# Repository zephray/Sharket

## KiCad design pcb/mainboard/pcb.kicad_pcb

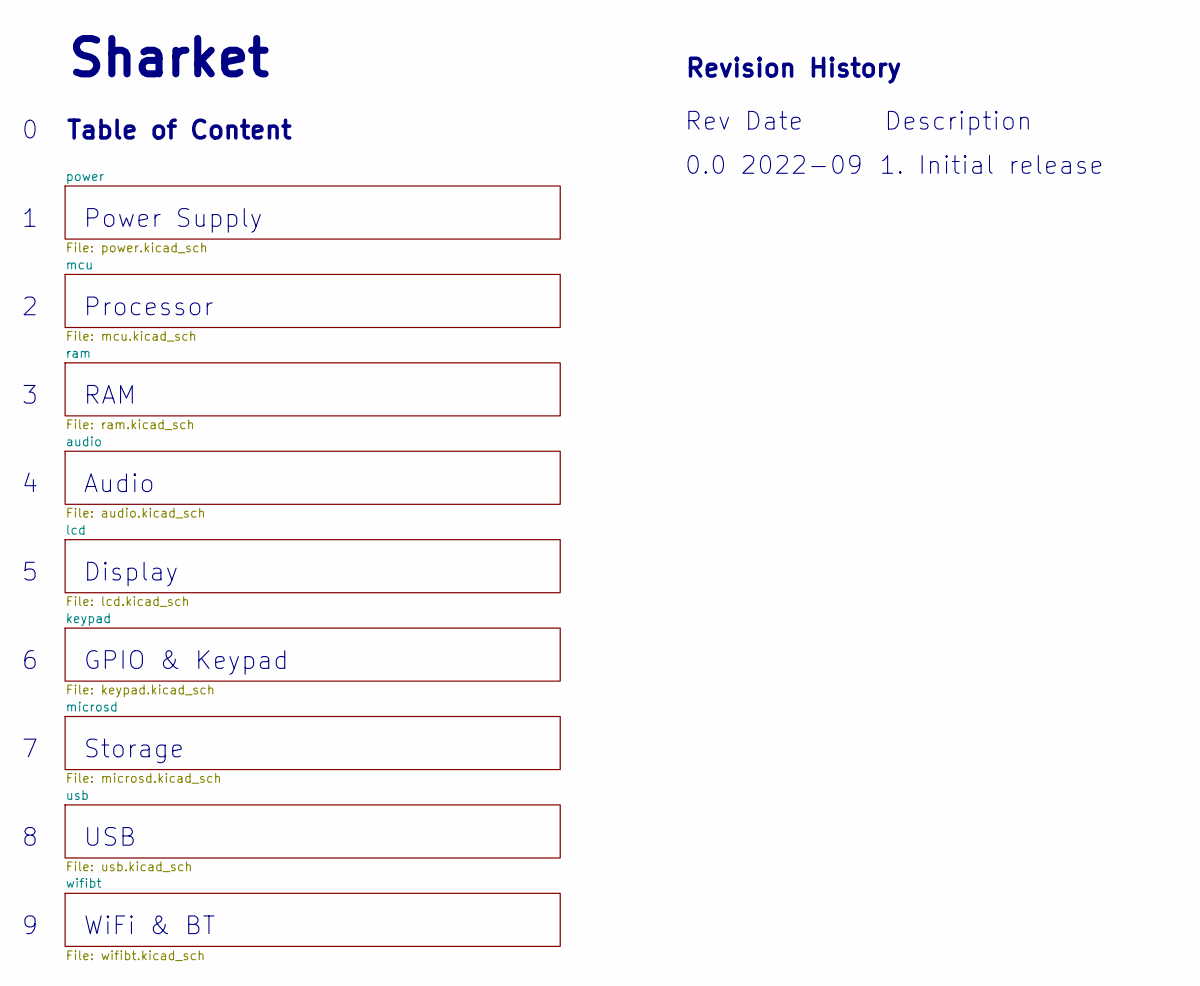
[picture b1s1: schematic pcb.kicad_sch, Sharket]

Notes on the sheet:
Storage
WiFi & BT
0.0 2022-09
Processor
Display
Revision History
Power Supply
Sharket
GPIO & Keypad
USB
Table of Content
RAM
Rev Date Description
Audio
1. Initial release

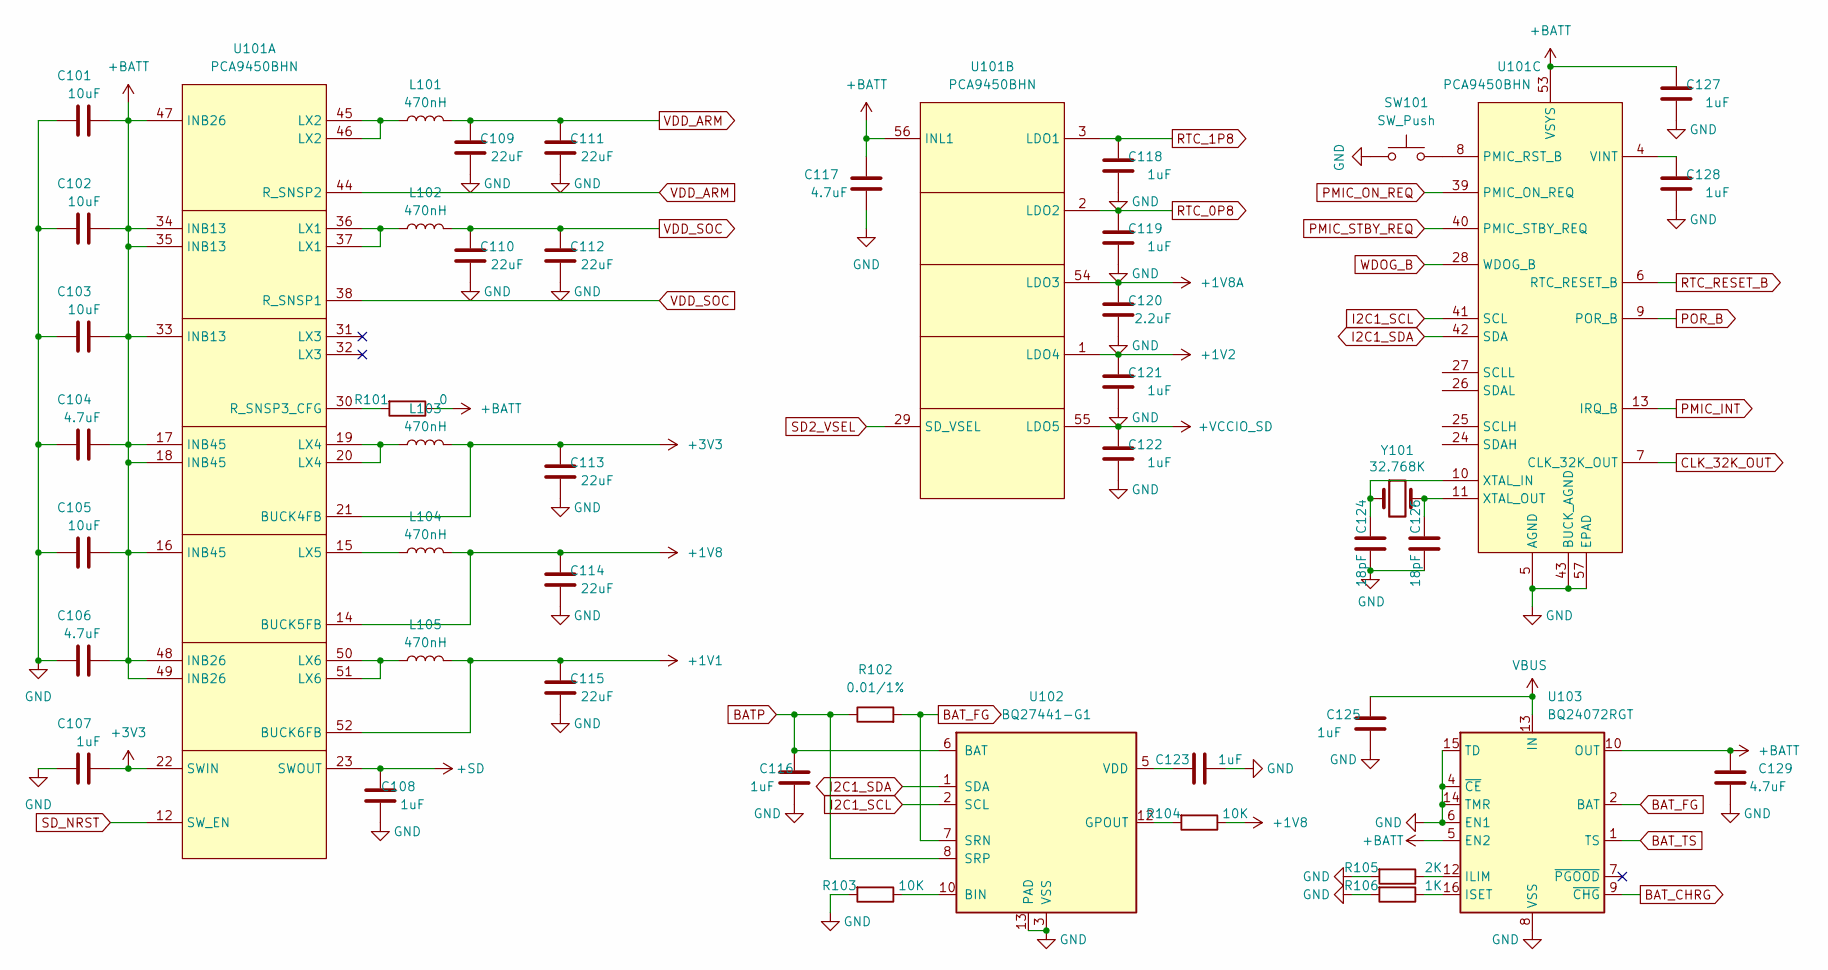
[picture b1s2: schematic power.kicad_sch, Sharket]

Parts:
C101, C102, C103, C105: 10uF; C_0603_1608Metric
C104, C106, C117, C129: 4.7uF; C_0402_1005Metric
C107, C108, C116, C123: 1uF; C_0402_1005Metric
C109, C110, C111, C112, C113, C114, C115: 22uF; C_0603_1608Metric
C118, C119, C121, C122, C125, C127, C128: 1uF; C_0201_0603Metric
C120: 2.2uF; C_0402_1005Metric
C124, C126: 18pF; C_0402_1005Metric
L101, L102, L103, L104, L105: 470nH; L_1008_2520Metric
R101: 0; R_0402_1005Metric
R102: 0.01/1%; R_0603_1608Metric
R103, R104: 10K; R_0402_1005Metric
R105: 2K; R_0402_1005Metric
R106: 1K; R_0402_1005Metric
SW101: SW_Push; SW_SPST_SKQG_WithStem
U101: PCA9450BHN; QFN-56_EP_7x7_Pitch0.4mm
U102: BQ27441-G1; Texas_S-PDSO-N12
U103: BQ24072RGT; VQFN-16-1EP_3x3mm_P0.5mm_EP1.6x1.6mm
Y101: 32.768K; Crystal_SMD_TXC_9HT11-2Pin_2.0x1.2mm_HandSoldering

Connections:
+1V1: C115.2, L105.2, U101.52 (BUCK6FB); also elsewhere on the board
+1V2: C121.2, U101.1 (LDO4); also elsewhere on the board
+1V8: C114.2, L104.2, R104.1, U101.14 (BUCK5FB); also elsewhere on the board
+1V8A: C120.2, U101.54 (LDO3); also elsewhere on the board
+3V3: C107.2, C113.2, L103.2, U101.21 (BUCK4FB), U101.22 (SWIN); also elsewhere on the board
+BATT: C101.2, C102.2, C103.2, C104.2, C105.2, C106.2, C117.2, C127.2, C129.2, R101.1, U101.16 (INB45), U101.17 (INB45), U101.18 (INB45), U101.33 (INB13), U101.34 (INB13), U101.35 (INB13), U101.47 (INB26), U101.48 (INB26), U101.49 (INB26), U101.53 (VSYS), U101.56 (INL1), U103.5 (EN2), U103.10 (OUT), U103.11 (OUT); also elsewhere on the board
+SD: C108.2, U101.23 (SWOUT); also elsewhere on the board
+VCCIO_SD: C122.2, U101.55 (LDO5); also elsewhere on the board
BATP: C116.2, R102.1, U102.6 (BAT), U102.8 (SRP); also elsewhere on the board
BAT_CHRG: U103.9 (~CHG)
BAT_FG: R102.2, U102.7 (SRN), U103.2 (BAT), U103.3 (BAT)
BAT_TS: U103.1 (TS)
CLK_32K_OUT: U101.7 (CLK_32K_OUT); also elsewhere on the board
GND: C101.1, C102.1, C103.1, C104.1, C105.1, C106.1, C107.1, C108.1, C109.1, C110.1, C111.1, C112.1, C113.1, C114.1, C115.1, C116.1, C117.1, C118.1, C119.1, C120.1, C121.1, C122.1, C123.1, C124.1, C125.1, C126.1, C127.1, C128.1, C129.1, R103.2, R105.2, R106.2, SW101.1, U101.5 (AGND), U101.43 (BUCK_AGND), U101.57 (EPAD), U102.3 (VSS), U102.13 (PAD), U103.4 (~CE), U103.6 (EN1), U103.8 (VSS), U103.14 (TMR), U103.15 (TD), U103.17 (VSS); also elsewhere on the board
I2C1_SCL: U101.41 (SCL), U102.2 (SCL); also elsewhere on the board
I2C1_SDA: U101.42 (SDA), U102.1 (SDA); also elsewhere on the board
unnamed: L101.1, U101.45 (LX2), U101.46 (LX2)
unnamed: L102.1, U101.36 (LX1), U101.37 (LX1)
unnamed: L103.1, U101.19 (LX4), U101.20 (LX4)
unnamed: L105.1, U101.50 (LX6), U101.51 (LX6)
unnamed: L104.1, U101.15 (LX5)
unnamed: R101.2, U101.30 (R_SNSP3_CFG)
unnamed: SW101.2, U101.8 (PMIC_RST_B)
unnamed: C128.2, U101.4 (VINT)
unnamed: C124.2, U101.10 (XTAL_IN), Y101.1
unnamed: C126.2, U101.11 (XTAL_OUT), Y101.2
unnamed: R103.1, U102.10 (BIN)
unnamed: R104.2, U102.12 (GPOUT)
unnamed: C123.2, U102.5 (VDD)
unnamed: R105.1, U103.12 (ILIM)
unnamed: R106.1, U103.16 (ISET)
PMIC_INT: U101.13 (IRQ_B); also elsewhere on the board
PMIC_ON_REQ: U101.39 (PMIC_ON_REQ); also elsewhere on the board
PMIC_STBY_REQ: U101.40 (PMIC_STBY_REQ); also elsewhere on the board
POR_B: U101.9 (POR_B); also elsewhere on the board
RTC_0P8: C119.2, U101.2 (LDO2); also elsewhere on the board
RTC_1P8: C118.2, U101.3 (LDO1); also elsewhere on the board
RTC_RESET_B: U101.6 (RTC_RESET_B); also elsewhere on the board
SD2_VSEL: U101.29 (SD_VSEL); also elsewhere on the board
SD_NRST: U101.12 (SW_EN); also elsewhere on the board
VBUS: C125.2, U103.13 (IN); also elsewhere on the board
VDD_ARM: C109.2, C111.2, L101.2, U101.44 (R_SNSP2); also elsewhere on the board
VDD_SOC: C110.2, C112.2, L102.2, U101.38 (R_SNSP1); also elsewhere on the board
WDOG_B: U101.28 (WDOG_B); also elsewhere on the board

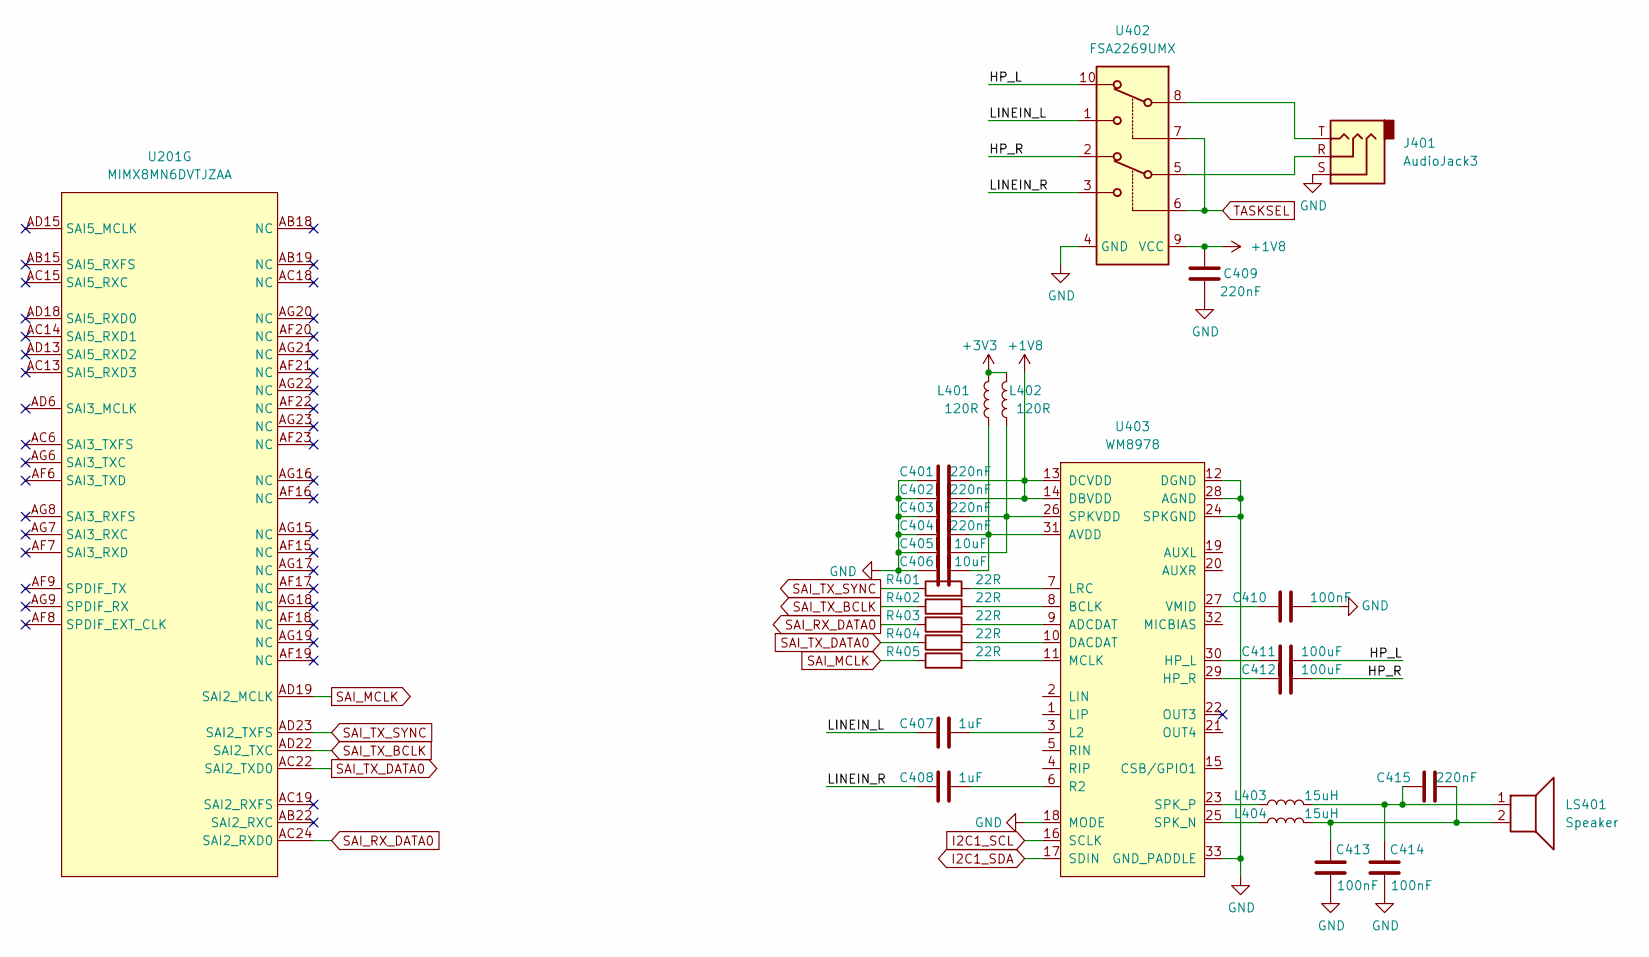
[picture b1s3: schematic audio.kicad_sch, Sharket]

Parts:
C401, C402, C403, C404, C409, C415: 220nF; C_0201_0603Metric; LCSC C880414
C405, C406: 10uF; C_0402_1005Metric; LCSC C105490
C407, C408: 1uF; C_0402_1005Metric; LCSC C157353
C410, C413, C414: 100nF; C_0201_0603Metric; LCSC C56392
C411, C412: 100uF; C_1206_3216Metric; LCSC C178304
J401: AudioJack3; PJ-208
L401, L402: 120R; L_0603_1608Metric; LCSC C76892
L403, L404: 15uH; L_0603_1608Metric; LCSC C486329
LS401: Speaker; Buzzer_CUI_CPT-9019S-SMT
R401, R402, R403, R404, R405: 22R; R_0402_1005Metric; LCSC C93929
U201: MIMX8MN6DVTJZAA; BGA-486_27x27_14.0x14.0mm
U402: FSA2269UMX; UQFN-10_1.4x1.8mm_P0.4mm
U403: WM8978; QFN-32-1EP_5x5mm_P0.5mm_EP3.45x3.45mm_ThermalVias

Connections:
+1V8: C401.1, C402.1, C409.1, U402.9 (VCC), U403.13 (DCVDD), U403.14 (DBVDD); also elsewhere on the board
+3V3: L401.2, L402.2; also elsewhere on the board
/audio/HP_L: C411.2, U402.10
/audio/HP_R: C412.2, U402.2
/audio/LINEIN_L: C407.2, U402.1
/audio/LINEIN_R: C408.2, U402.3
GND: C401.2, C402.2, C403.2, C404.2, C405.2, C406.2, C409.2, C410.2, C413.1, C414.1, J401.S, U402.4 (GND), U403.12 (DGND), U403.18 (MODE), U403.24 (SPKGND), U403.28 (AGND), U403.33 (GND_PADDLE); also elsewhere on the board
I2C1_SCL: U403.16 (SCLK); also elsewhere on the board
I2C1_SDA: U403.17 (SDIN); also elsewhere on the board
unnamed: C413.2, C415.2, L404.2, LS401.2
unnamed: C414.2, C415.1, L403.2, LS401.1
unnamed: J401.R, U402.5
unnamed: J401.T, U402.8
unnamed: R403.2, U403.9 (ADCDAT)
unnamed: C404.1, C406.1, L401.1, U403.31 (AVDD)
unnamed: R402.2, U403.8 (BCLK)
unnamed: R404.2, U403.10 (DACDAT)
unnamed: C411.1, U403.30 (HP_L)
unnamed: C412.1, U403.29 (HP_R)
unnamed: C407.1, U403.3 (L2)
unnamed: R401.2, U403.7 (LRC)
unnamed: R405.2, U403.11 (MCLK)
unnamed: C408.1, U403.6 (R2)
unnamed: C403.1, C405.1, L402.1, U403.26 (SPKVDD)
unnamed: L404.1, U403.25 (SPK_N)
unnamed: L403.1, U403.23 (SPK_P)
unnamed: C410.1, U403.27 (VMID)
SAI_MCLK: R405.1, U201.AD19 (SAI2_MCLK)
SAI_RX_DATA0: R403.1, U201.AC24 (SAI2_RXD0)
SAI_TX_BCLK: R402.1, U201.AD22 (SAI2_TXC)
SAI_TX_DATA0: R404.1, U201.AC22 (SAI2_TXD0)
SAI_TX_SYNC: R401.1, U201.AD23 (SAI2_TXFS)
TASKSEL: U402.6, U402.7; also elsewhere on the board

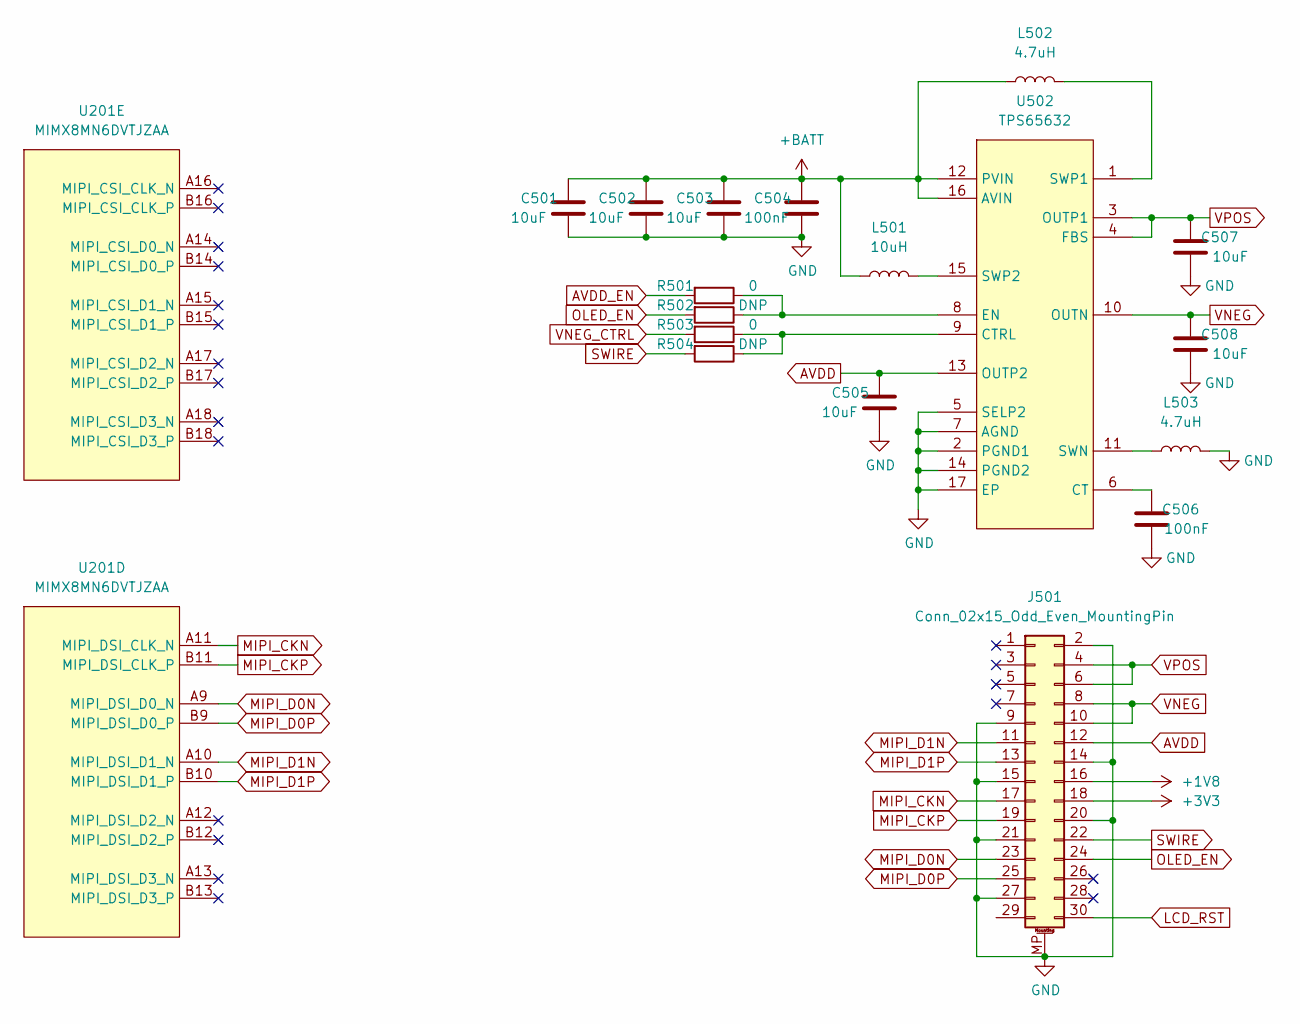
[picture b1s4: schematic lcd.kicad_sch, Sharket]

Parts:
C501, C502, C503, C505, C507, C508: 10uF; C_0603_1608Metric
C504, C506: 100nF; C_0201_0603Metric
J501: Conn_02x15_Odd_Even_MountingPin; 505270-3012
L501: 10uH; L_1008_2520Metric
L502, L503: 4.7uH; L_1008_2520Metric
R501, R503: 0; R_0402_1005Metric
R502, R504: DNP; R_0402_1005Metric
U201: MIMX8MN6DVTJZAA; BGA-486_27x27_14.0x14.0mm
U502: TPS65632; QFN-16-1EP_3x3mm_P0.5mm_EP1.7x1.7mm

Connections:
+1V8: J501.16; also elsewhere on the board
+3V3: J501.18; also elsewhere on the board
+BATT: C501.2, C502.2, C503.2, C504.2, L501.1, L502.1, U502.12 (PVIN), U502.16 (AVIN); also elsewhere on the board
AVDD: C505.2, J501.12, U502.13 (OUTP2)
AVDD_EN: R501.2; also elsewhere on the board
GND: C501.1, C502.1, C503.1, C504.1, C505.1, C506.1, C507.1, C508.1, J501.2, J501.9, J501.14, J501.15, J501.20, J501.21, J501.27, J501.MP (MountPin), L503.2, U502.2 (PGND1), U502.5 (SELP2), U502.7 (AGND), U502.14 (PGND2), U502.17 (EP); also elsewhere on the board
LCD_RST: J501.30; also elsewhere on the board
MIPI_CKN: J501.17, U201.A11 (MIPI_DSI_CLK_N)
MIPI_CKP: J501.19, U201.B11 (MIPI_DSI_CLK_P)
MIPI_D0N: J501.23, U201.A9 (MIPI_DSI_D0_N)
MIPI_D0P: J501.25, U201.B9 (MIPI_DSI_D0_P)
MIPI_D1N: J501.11, U201.A10 (MIPI_DSI_D1_N)
MIPI_D1P: J501.13, U201.B10 (MIPI_DSI_D1_P)
unnamed: C506.2, U502.6 (CT)
unnamed: R503.1, R504.1, U502.9 (CTRL)
unnamed: R501.1, R502.1, U502.8 (EN)
unnamed: L503.1, U502.11 (SWN)
unnamed: L502.2, U502.1 (SWP1)
unnamed: L501.2, U502.15 (SWP2)
OLED_EN: J501.24, R502.2
SWIRE: J501.22, R504.2
VNEG: C508.2, J501.8, J501.10, U502.10 (OUTN)
VNEG_CTRL: R503.2; also elsewhere on the board
VPOS: C507.2, J501.4, J501.6, U502.3 (OUTP1), U502.4 (FBS)

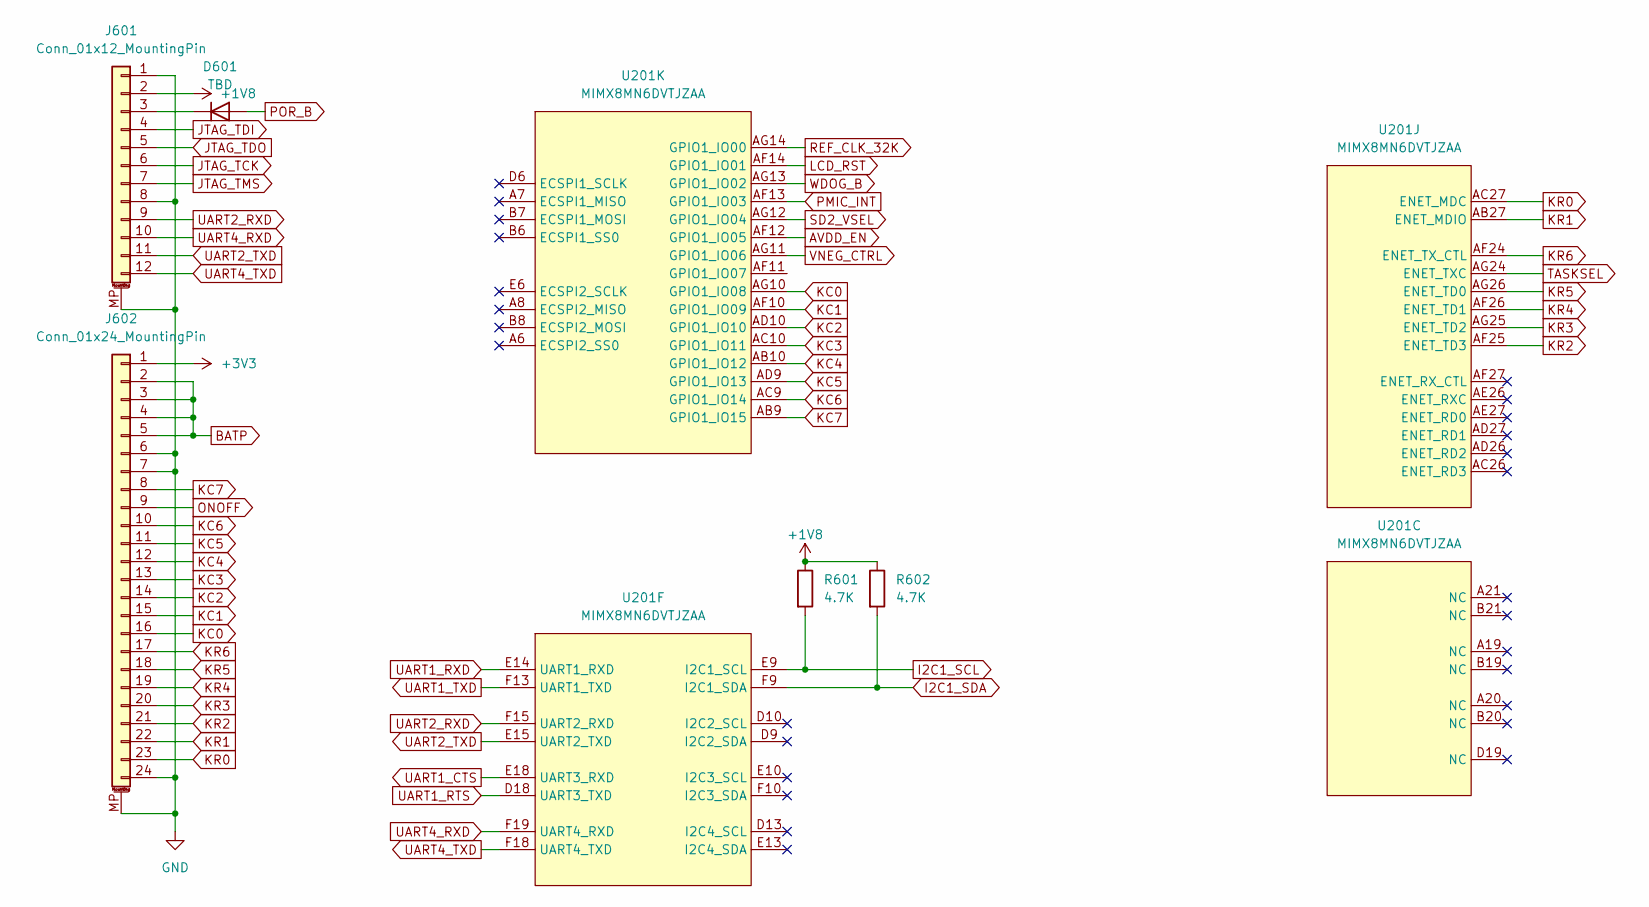
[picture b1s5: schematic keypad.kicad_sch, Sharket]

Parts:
D601: TBD; D_SOD-323
J601: Conn_01x12_MountingPin; TE_1-1734839-2_1x12-1MP_P0.5mm_Horizontal
J602: Conn_01x24_MountingPin; TE_2-1734839-4_1x24-1MP_P0.5mm_Horizontal
R601, R602: 4.7K; R_0402_1005Metric
U201: MIMX8MN6DVTJZAA; BGA-486_27x27_14.0x14.0mm

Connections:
+1V8: J601.2, R601.1, R602.1; also elsewhere on the board
+3V3: J602.1; also elsewhere on the board
AVDD_EN: U201.AF12 (GPIO1_IO05); also elsewhere on the board
BATP: J602.2, J602.3, J602.4, J602.5; also elsewhere on the board
GND: J601.1, J601.8, J601.MP (MountPin), J602.6, J602.7, J602.24, J602.MP (MountPin); also elsewhere on the board
I2C1_SCL: R601.2, U201.E9 (I2C1_SCL); also elsewhere on the board
I2C1_SDA: R602.2, U201.F9 (I2C1_SDA); also elsewhere on the board
JTAG_TCK: J601.6; also elsewhere on the board
JTAG_TDI: J601.4; also elsewhere on the board
JTAG_TDO: J601.5; also elsewhere on the board
JTAG_TMS: J601.7; also elsewhere on the board
KC0: J602.16, U201.AG10 (GPIO1_IO08)
KC1: J602.15, U201.AF10 (GPIO1_IO09)
KC2: J602.14, U201.AD10 (GPIO1_IO10)
KC3: J602.13, U201.AC10 (GPIO1_IO11)
KC4: J602.12, U201.AB10 (GPIO1_IO12)
KC5: J602.11, U201.AD9 (GPIO1_IO13)
KC6: J602.10, U201.AC9 (GPIO1_IO14)
KC7: J602.8, U201.AB9 (GPIO1_IO15)
KR0: J602.23, U201.AC27 (ENET_MDC)
KR1: J602.22, U201.AB27 (ENET_MDIO)
KR2: J602.21, U201.AF25 (ENET_TD3)
KR3: J602.20, U201.AG25 (ENET_TD2)
KR4: J602.19, U201.AF26 (ENET_TD1)
KR5: J602.18, U201.AG26 (ENET_TD0)
KR6: J602.17, U201.AF24 (ENET_TX_CTL)
LCD_RST: U201.AF14 (GPIO1_IO01); also elsewhere on the board
unnamed: D601.1 (K), J601.3
ONOFF: J602.9; also elsewhere on the board
PMIC_INT: U201.AF13 (GPIO1_IO03); also elsewhere on the board
POR_B: D601.2 (A); also elsewhere on the board
REF_CLK_32K: U201.AG14 (GPIO1_IO00); also elsewhere on the board
SD2_VSEL: U201.AG12 (GPIO1_IO04); also elsewhere on the board
TASKSEL: U201.AG24 (ENET_TXC); also elsewhere on the board
UART1_CTS: U201.E18 (UART3_RXD); also elsewhere on the board
UART1_RTS: U201.D18 (UART3_TXD); also elsewhere on the board
UART1_RXD: U201.E14 (UART1_RXD); also elsewhere on the board
UART1_TXD: U201.F13 (UART1_TXD); also elsewhere on the board
UART2_RXD: J601.9, U201.F15 (UART2_RXD)
UART2_TXD: J601.11, U201.E15 (UART2_TXD)
UART4_RXD: J601.10, U201.F19 (UART4_RXD)
UART4_TXD: J601.12, U201.F18 (UART4_TXD)
VNEG_CTRL: U201.AG11 (GPIO1_IO06); also elsewhere on the board
WDOG_B: U201.AG13 (GPIO1_IO02); also elsewhere on the board

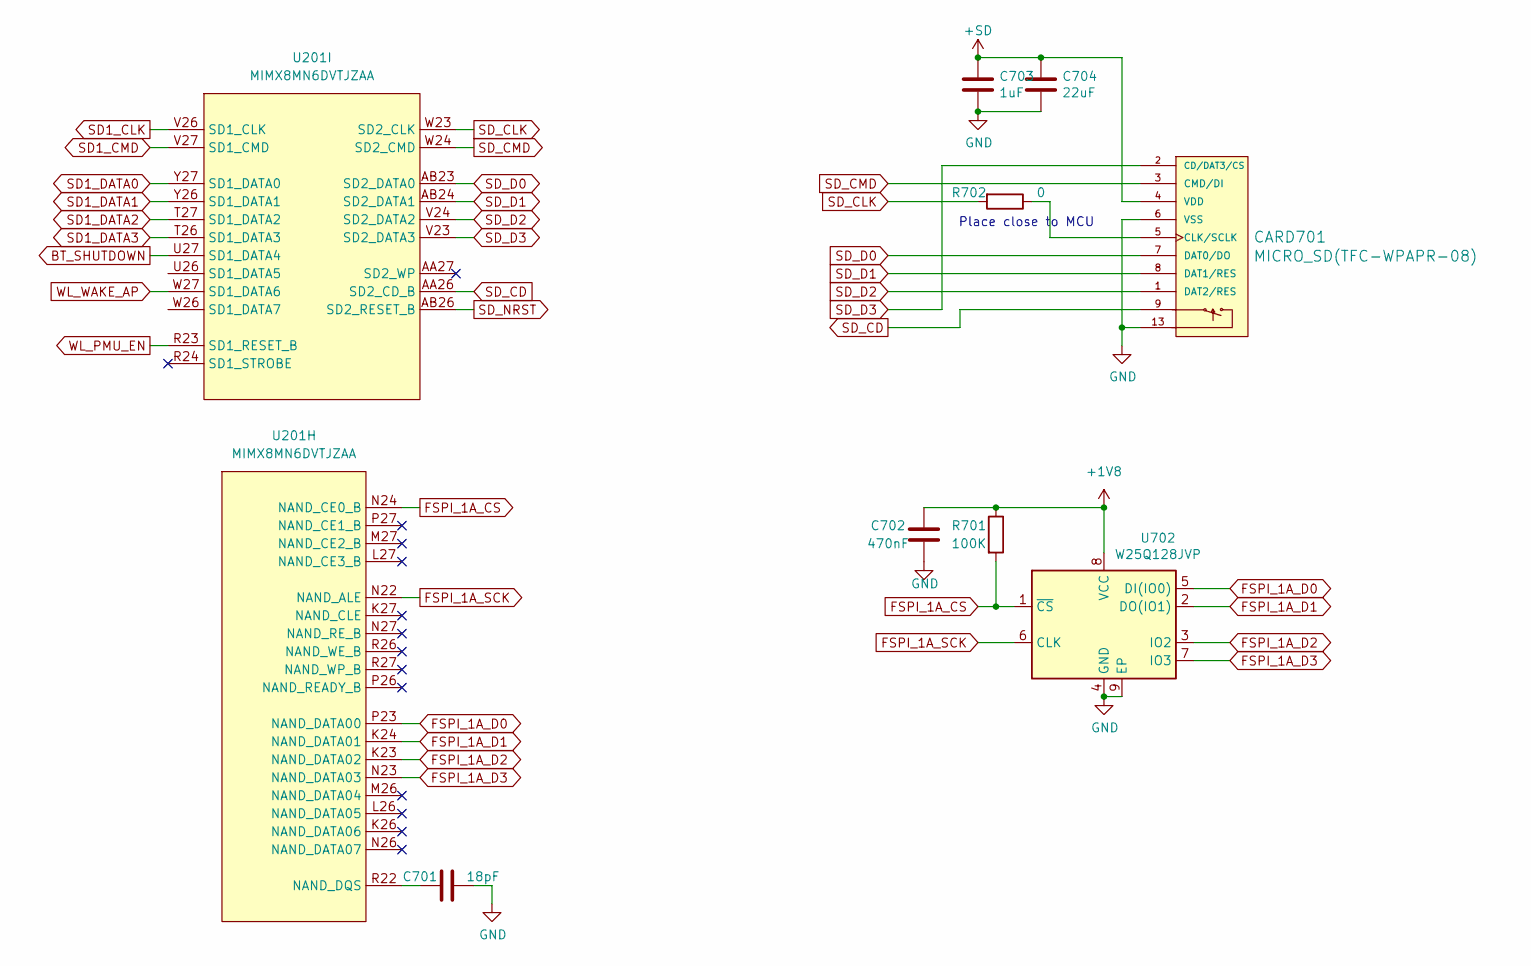
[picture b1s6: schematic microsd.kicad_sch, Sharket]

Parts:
C701: 18pF; C_0402_1005Metric
C702: 470nF; C_0402_1005Metric
C703: 1uF; C_0402_1005Metric
C704: 22uF; C_0603_1608Metric
CARD701: MICRO_SD(TFC-WPAPR-08); TFC-WPAPR-08
R701: 100K; R_0402_1005Metric
R702: 0; R_0402_1005Metric
U201: MIMX8MN6DVTJZAA; BGA-486_27x27_14.0x14.0mm
U702: W25Q128JVP; WSON-8-1EP_6x5mm_P1.27mm_EP3.4x4.3mm

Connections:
+1V8: C702.2, R701.1, U702.8 (VCC); also elsewhere on the board
+SD: C703.1, C704.1, CARD701.4 (VDD); also elsewhere on the board
BT_SHUTDOWN: U201.U27 (SD1_DATA4); also elsewhere on the board
FSPI_1A_CS: R701.2, U201.N24 (NAND_CE0_B), U702.1 (~CS)
FSPI_1A_D0: U201.P23 (NAND_DATA00), U702.5 (DI(IO0))
FSPI_1A_D1: U201.K24 (NAND_DATA01), U702.2 (DO(IO1))
FSPI_1A_D2: U201.K23 (NAND_DATA02), U702.3 (IO2)
FSPI_1A_D3: U201.N23 (NAND_DATA03), U702.7 (IO3)
FSPI_1A_SCK: U201.N22 (NAND_ALE), U702.6 (CLK)
GND: C701.1, C702.1, C703.2, C704.2, CARD701.6 (VSS), CARD701.10, CARD701.11, CARD701.12, CARD701.13, U702.4 (GND), U702.9 (EP); also elsewhere on the board
unnamed: CARD701.5 (CLK/SCLK), R702.1
unnamed: C701.2, U201.R22 (NAND_DQS)
SD1_CLK: U201.V26 (SD1_CLK); also elsewhere on the board
SD1_CMD: U201.V27 (SD1_CMD); also elsewhere on the board
SD1_DATA0: U201.Y27 (SD1_DATA0); also elsewhere on the board
SD1_DATA1: U201.Y26 (SD1_DATA1); also elsewhere on the board
SD1_DATA2: U201.T27 (SD1_DATA2); also elsewhere on the board
SD1_DATA3: U201.T26 (SD1_DATA3); also elsewhere on the board
SD_CD: CARD701.9, U201.AA26 (SD2_CD_B)
SD_CLK: R702.2, U201.W23 (SD2_CLK)
SD_CMD: CARD701.3 (CMD/DI), U201.W24 (SD2_CMD)
SD_D0: CARD701.7 (DAT0/DO), U201.AB23 (SD2_DATA0)
SD_D1: CARD701.8 (DAT1/RES), U201.AB24 (SD2_DATA1)
SD_D2: CARD701.1 (DAT2/RES), U201.V24 (SD2_DATA2)
SD_D3: CARD701.2 (CD/DAT3/CS), U201.V23 (SD2_DATA3)
SD_NRST: U201.AB26 (SD2_RESET_B); also elsewhere on the board
WL_PMU_EN: U201.R23 (SD1_RESET_B); also elsewhere on the board
WL_WAKE_AP: U201.W27 (SD1_DATA6); also elsewhere on the board

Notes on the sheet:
Place close to MCU

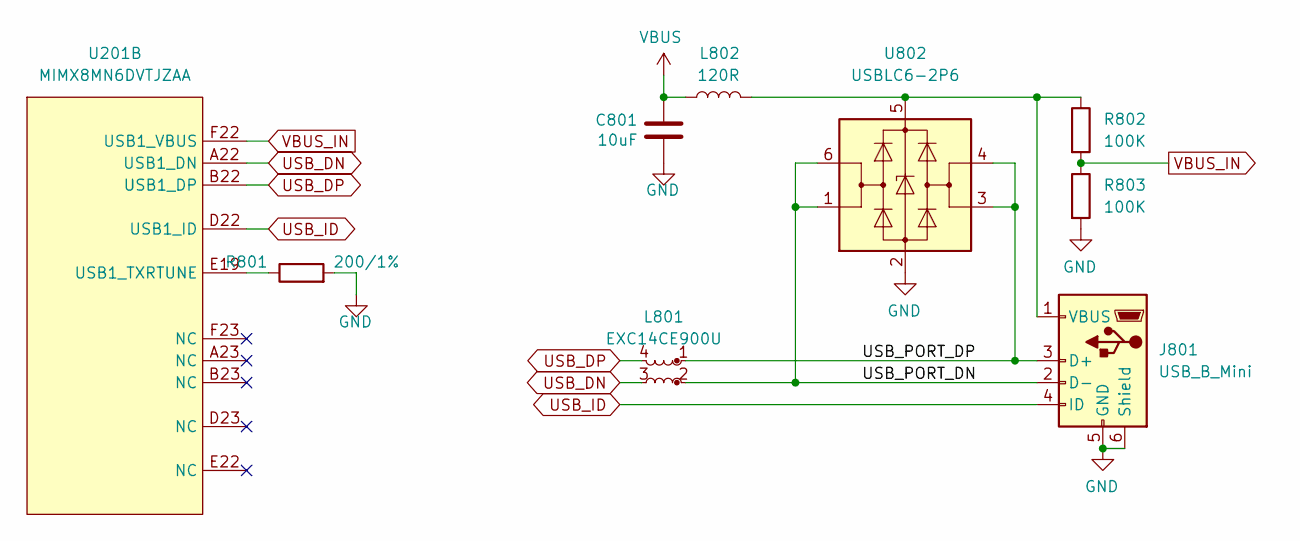
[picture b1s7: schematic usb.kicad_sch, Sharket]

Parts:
C801: 10uF; C_0402_1005Metric
J801: USB_B_Mini; USB_Mini-B_Wuerth_65100516121_Horizontal
L801: EXC14CE900U; L_CommonModeChoke_Panasonic_EXC14CE
L802: 120R; L_0603_1608Metric
R801: 200/1%; R_0402_1005Metric
R802, R803: 100K; R_0402_1005Metric
U201: MIMX8MN6DVTJZAA; BGA-486_27x27_14.0x14.0mm
U802: USBLC6-2P6; SOT-666

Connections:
/usb/USB_PORT_DN: J801.2 (D-), L801.2, U802.1 (I/O1), U802.6 (I/O1)
/usb/USB_PORT_DP: J801.3 (D+), L801.1, U802.3 (I/O2), U802.4 (I/O2)
GND: C801.2, J801.5 (GND), J801.6 (Shield), R801.2, R803.2, U802.2 (GND); also elsewhere on the board
unnamed: J801.1 (VBUS), L802.2, R802.1, U802.5 (VBUS)
unnamed: R801.1, U201.E19 (USB1_TXRTUNE)
USB_DN: L801.3, U201.A22 (USB1_DN)
USB_DP: L801.4, U201.B22 (USB1_DP)
USB_ID: J801.4 (ID), U201.D22 (USB1_ID)
VBUS: C801.1, L802.1; also elsewhere on the board
VBUS_IN: R802.2, R803.1, U201.F22 (USB1_VBUS)

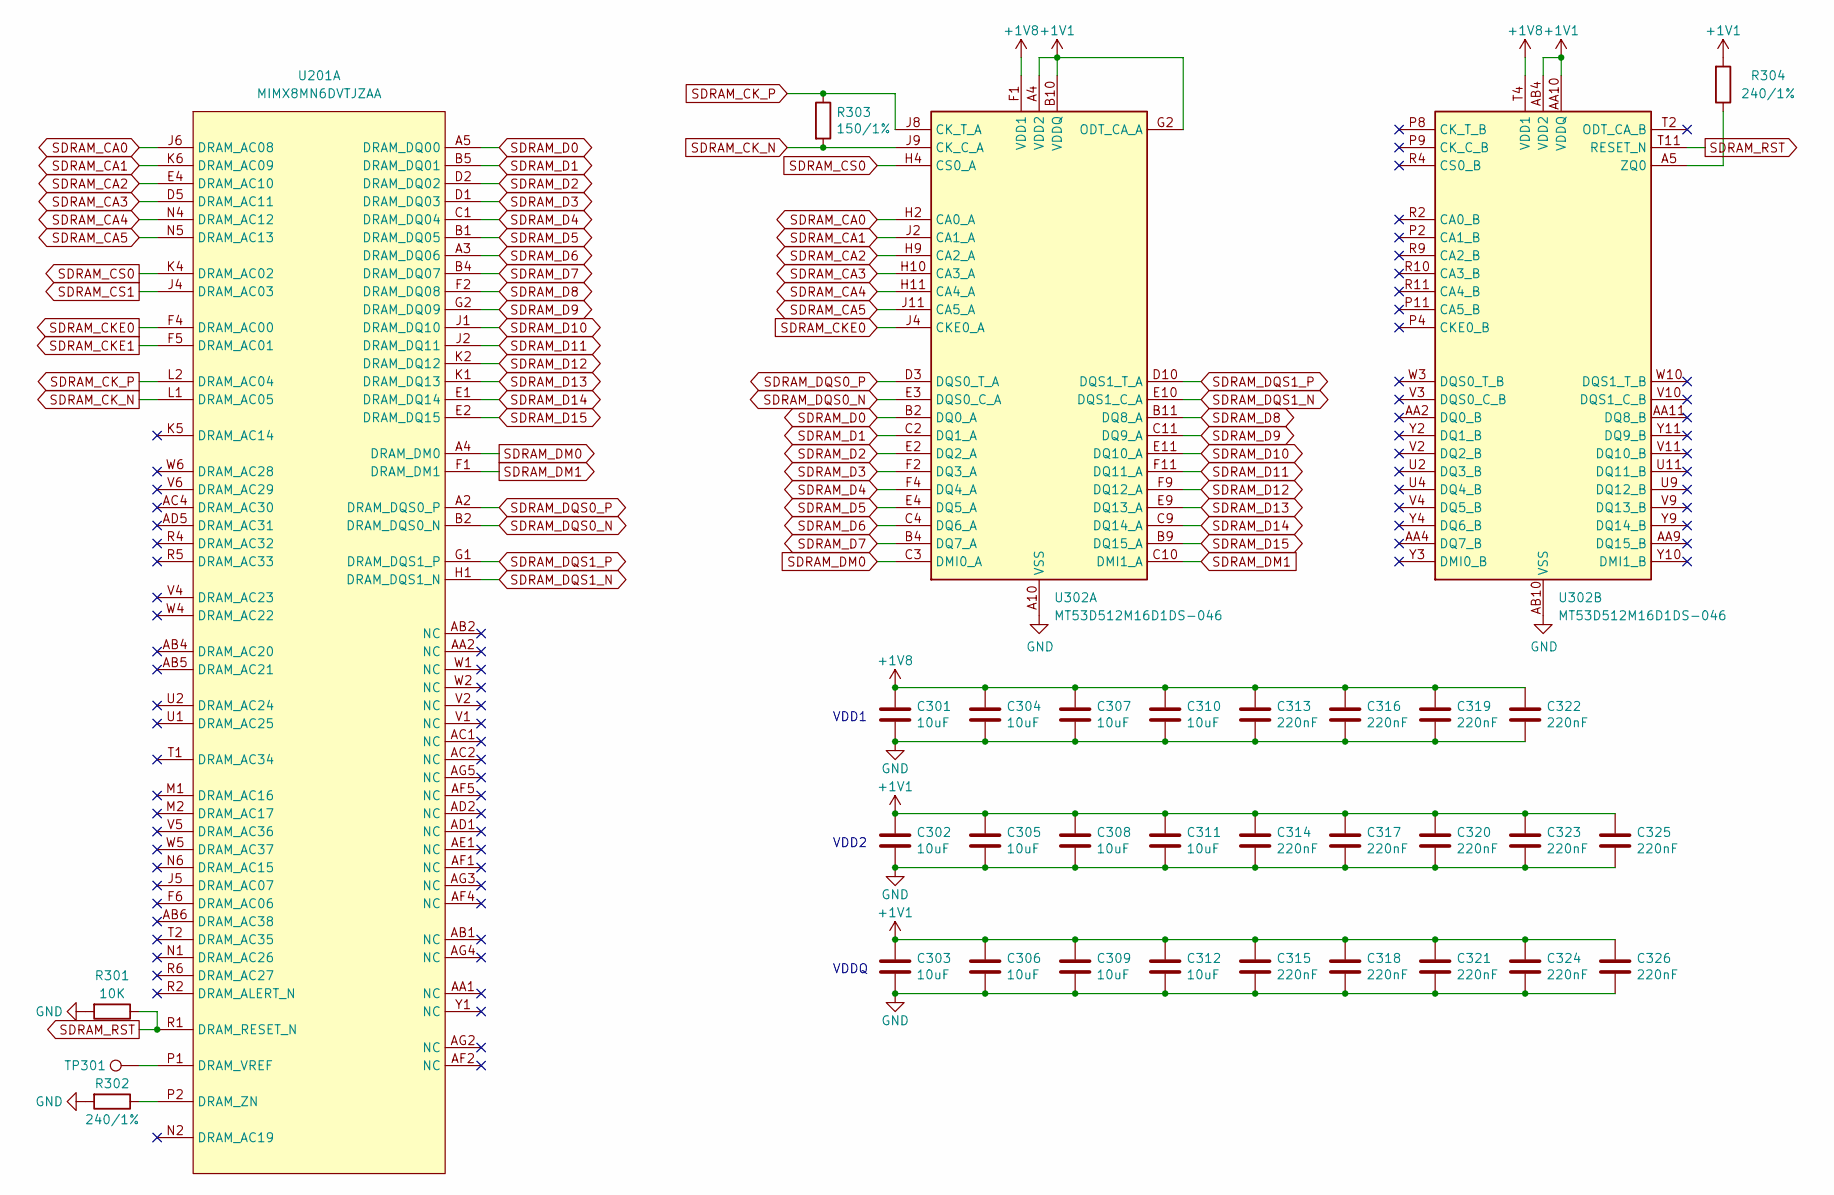
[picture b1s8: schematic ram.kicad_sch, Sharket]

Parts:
C301, C302, C303, C304, C305, C306, C307, C308, C309, C310, C311, C312: 10uF; C_0402_1005Metric
C313, C314, C315, C316, C317, C318, C319, C320, C321, C322, C323, C324, C325, C326: 220nF; C_0201_0603Metric
R301: 10K; R_0402_1005Metric
R302, R304: 240/1%; R_0402_1005Metric
R303: 150/1%; R_0402_1005Metric
TP301: TestPoint; TestPoint_Pad_D1.0mm
U201: MIMX8MN6DVTJZAA; BGA-486_27x27_14.0x14.0mm
U302: MT53D512M16D1DS-046; BGA-200_10.0x14.5mm_Layout12x22_P0.80x0.65mm_B0.3mm

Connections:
+1V1: C302.1, C303.1, C305.1, C306.1, C308.1, C309.1, C311.1, C312.1, C314.1, C315.1, C317.1, C318.1, C320.1, C321.1, C323.1, C324.1, C325.1, C326.1, R304.2, U302.A4 (VDD2), U302.A9 (VDD2), U302.AA3 (VDDQ), U302.AA5 (VDDQ), U302.AA8 (VDDQ), U302.AA10 (VDDQ), U302.AB4 (VDD2), U302.AB9 (VDD2), U302.B3 (VDDQ), U302.B5 (VDDQ), U302.B8 (VDDQ), U302.B10 (VDDQ), U302.D1 (VDDQ), U302.D5 (VDDQ), U302.D8 (VDDQ), U302.D12 (VDDQ), U302.F3 (VDDQ), U302.F5 (VDD2), U302.F8 (VDD2), U302.F10 (VDDQ), U302.G2 (ODT_CA_A), U302.H1 (VDD2), U302.H5 (VDD2), U302.H8 (VDD2), U302.H12 (VDD2), U302.K1 (VDD2), U302.K3 (VDD2), U302.K10 (VDD2), U302.K12 (VDD2), U302.N1 (VDD2), U302.N3 (VDD2), U302.N10 (VDD2), U302.N12 (VDD2), U302.R1 (VDD2), U302.R5 (VDD2), U302.R8 (VDD2), U302.R12 (VDD2), U302.U3 (VDDQ), U302.U5 (VDD2), U302.U8 (VDD2), U302.U10 (VDDQ), U302.W1 (VDDQ), U302.W5 (VDDQ), U302.W8 (VDDQ), U302.W12 (VDDQ); also elsewhere on the board
+1V8: C301.1, C304.1, C307.1, C310.1, C313.1, C316.1, C319.1, C322.1, U302.F1 (VDD1), U302.F12 (VDD1), U302.G4 (VDD1), U302.G9 (VDD1), U302.T4 (VDD1), U302.T9 (VDD1), U302.U1 (VDD1), U302.U12 (VDD1); also elsewhere on the board
GND: C301.2, C302.2, C303.2, C304.2, C305.2, C306.2, C307.2, C308.2, C309.2, C310.2, C311.2, C312.2, C313.2, C314.2, C315.2, C316.2, C317.2, C318.2, C319.2, C320.2, C321.2, C322.2, C323.2, C324.2, C325.2, C326.2, R301.2, R302.2, U302.A3 (VSS), U302.A10 (VSS), U302.AB3 (VSS), U302.AB5 (VSS), U302.AB8 (VSS), U302.AB10 (VSS), U302.C1 (VSS), U302.C5 (VSS), U302.C8 (VSS), U302.C12 (VSS), U302.D2 (VSS), U302.D4 (VSS), U302.D9 (VSS), U302.D11 (VSS), U302.E1 (VSS), U302.E5 (VSS), U302.E8 (VSS), U302.E12 (VSS), U302.G1 (VSS), U302.G3 (VSS), U302.G5 (VSS), U302.G8 (VSS), U302.G10 (VSS), U302.G12 (VSS), U302.J1 (VSS), U302.J3 (VSS), U302.J10 (VSS), U302.J12 (VSS), U302.K2 (VSS), U302.K4 (VSS), U302.K9 (VSS), U302.K11 (VSS), U302.N2 (VSS), U302.N4 (VSS), U302.N9 (VSS), U302.N11 (VSS), U302.P1 (VSS), U302.P3 (VSS), U302.P10 (VSS), U302.P12 (VSS), U302.T1 (VSS), U302.T3 (VSS), U302.T5 (VSS), U302.T8 (VSS), U302.T10 (VSS), U302.T12 (VSS), U302.V1 (VSS), U302.V5 (VSS), U302.V8 (VSS), U302.V12 (VSS), U302.W2 (VSS), U302.W4 (VSS), U302.W9 (VSS), U302.W11 (VSS), U302.Y1 (VSS), U302.Y5 (VSS), U302.Y8 (VSS), U302.Y12 (VSS); also elsewhere on the board
unnamed: TP301.1, U201.P1 (DRAM_VREF)
unnamed: R302.1, U201.P2 (DRAM_ZN)
unnamed: R304.1, U302.A5 (ZQ0)
SDRAM_CA0: U201.J6 (DRAM_AC08), U302.H2 (CA0_A)
SDRAM_CA1: U201.K6 (DRAM_AC09), U302.J2 (CA1_A)
SDRAM_CA2: U201.E4 (DRAM_AC10), U302.H9 (CA2_A)
SDRAM_CA3: U201.D5 (DRAM_AC11), U302.H10 (CA3_A)
SDRAM_CA4: U201.N4 (DRAM_AC12), U302.H11 (CA4_A)
SDRAM_CA5: U201.N5 (DRAM_AC13), U302.J11 (CA5_A)
SDRAM_CKE0: U201.F4 (DRAM_AC00), U302.J4 (CKE0_A)
SDRAM_CKE1: U201.F5 (DRAM_AC01)
SDRAM_CK_N: R303.2, U201.L1 (DRAM_AC05), U302.J9 (CK_C_A)
SDRAM_CK_P: R303.1, U201.L2 (DRAM_AC04), U302.J8 (CK_T_A)
SDRAM_CS0: U201.K4 (DRAM_AC02), U302.H4 (CS0_A)
SDRAM_CS1: U201.J4 (DRAM_AC03)
SDRAM_D0: U201.A5 (DRAM_DQ00), U302.B2 (DQ0_A)
SDRAM_D1: U201.B5 (DRAM_DQ01), U302.C2 (DQ1_A)
SDRAM_D2: U201.D2 (DRAM_DQ02), U302.E2 (DQ2_A)
SDRAM_D3: U201.D1 (DRAM_DQ03), U302.F2 (DQ3_A)
SDRAM_D4: U201.C1 (DRAM_DQ04), U302.F4 (DQ4_A)
SDRAM_D5: U201.B1 (DRAM_DQ05), U302.E4 (DQ5_A)
SDRAM_D6: U201.A3 (DRAM_DQ06), U302.C4 (DQ6_A)
SDRAM_D7: U201.B4 (DRAM_DQ07), U302.B4 (DQ7_A)
SDRAM_D8: U201.F2 (DRAM_DQ08), U302.B11 (DQ8_A)
SDRAM_D9: U201.G2 (DRAM_DQ09), U302.C11 (DQ9_A)
SDRAM_D10: U201.J1 (DRAM_DQ10), U302.E11 (DQ10_A)
SDRAM_D11: U201.J2 (DRAM_DQ11), U302.F11 (DQ11_A)
SDRAM_D12: U201.K2 (DRAM_DQ12), U302.F9 (DQ12_A)
SDRAM_D13: U201.K1 (DRAM_DQ13), U302.E9 (DQ13_A)
SDRAM_D14: U201.E1 (DRAM_DQ14), U302.C9 (DQ14_A)
SDRAM_D15: U201.E2 (DRAM_DQ15), U302.B9 (DQ15_A)
SDRAM_DM0: U201.A4 (DRAM_DM0), U302.C3 (DMI0_A)
SDRAM_DM1: U201.F1 (DRAM_DM1), U302.C10 (DMI1_A)
SDRAM_DQS0_N: U201.B2 (DRAM_DQS0_N), U302.E3 (DQS0_C_A)
SDRAM_DQS0_P: U201.A2 (DRAM_DQS0_P), U302.D3 (DQS0_T_A)
SDRAM_DQS1_N: U201.H1 (DRAM_DQS1_N), U302.E10 (DQS1_C_A)
SDRAM_DQS1_P: U201.G1 (DRAM_DQS1_P), U302.D10 (DQS1_T_A)
SDRAM_RST: R301.1, U201.R1 (DRAM_RESET_N), U302.T11 (RESET_N)

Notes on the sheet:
VDDQ
VDD1
VDD2

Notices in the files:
pcb/mainboard/wifibt.kicad_sch:
This source describes Open Hardware and is licensed under the CERN-OHL-P v2.
